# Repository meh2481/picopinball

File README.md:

# picopinball
Physical Pi Pico-Powered Pinball table heavily inspired by Space Cadet

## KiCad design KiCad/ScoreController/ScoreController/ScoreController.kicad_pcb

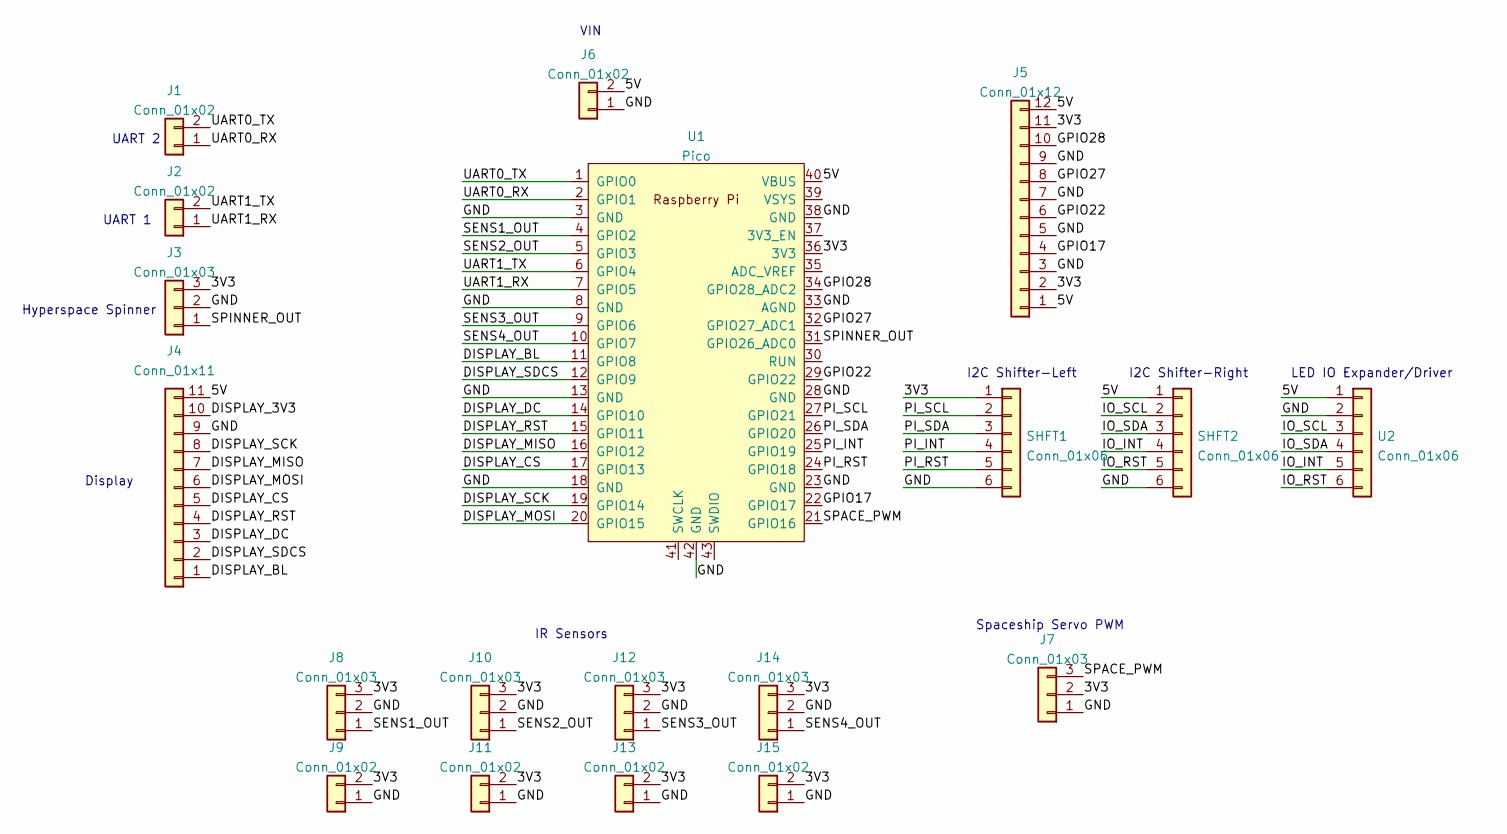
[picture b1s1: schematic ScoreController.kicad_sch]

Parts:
J1, J2, J9, J11, J13, J15: Conn_01x02; JST_XH_B2B-XH-A_1x02_P2.50mm_Vertical
J3, J8, J10, J12, J14: Conn_01x03; JST_XH_B3B-XH-A_1x03_P2.50mm_Vertical
J4: Conn_01x11; PinHeader_1x11_P2.54mm_Vertical
J5: Conn_01x12; TerminalBlock_Phoenix_MPT-0,5-12-2.54_1x12_P2.54mm_Horizont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
J6: Conn_01x02; TerminalBlock_4Ucon_1x02_P3.50mm_Horizontal
J7: Conn_01x03; PinHeader_1x03_P2.54mm_Vertical
SHFT1, SHFT2: Conn_01x06; PinHeader_1x06_P2.54mm_Vertical
U1: Pico; RPi_Pico_SMD
U2: Conn_01x06; PinHeader_1x06_P2.54mm_Vertical

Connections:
/3V3: J3.3, J5.2, J5.11, J7.2, J8.3, J9.2, J10.3, J11.2, J12.3, J13.2, J14.3, J15.2, SHFT1.1, U1.36 (3V3)
/5V: J4.11, J5.1, J5.12, J6.2, SHFT2.1, U1.40 (VBUS), U2.1
/DISPLAY_3V3: J4.10
/DISPLAY_BL: J4.1, U1.11 (GPIO8)
/DISPLAY_CS: J4.5, U1.17 (GPIO13)
/DISPLAY_DC: J4.3, U1.14 (GPIO10)
/DISPLAY_MISO: J4.7, U1.16 (GPIO12)
/DISPLAY_MOSI: J4.6, U1.20 (GPIO15)
/DISPLAY_RST: J4.4, U1.15 (GPIO11)
/DISPLAY_SCK: J4.8, U1.19 (GPIO14)
/DISPLAY_SDCS: J4.2, U1.12 (GPIO9)
/GND: J3.2, J4.9, J5.3, J5.5, J5.7, J5.9, J6.1, J7.1, J8.2, J9.1, J10.2, J11.1, J12.2, J13.1, J14.2, J15.1, SHFT1.6, SHFT2.6, U1.3 (GND), U1.8 (GND), U1.13 (GND), U1.18 (GND), U1.23 (GND), U1.28 (GND), U1.33 (AGND), U1.38 (GND), U1.42 (GND), U2.2
/GPIO17: J5.4, U1.22 (GPIO17)
/GPIO22: J5.6, U1.29 (GPIO22)
/GPIO27: J5.8, U1.32 (GPIO27_ADC1)
/GPIO28: J5.10, U1.34 (GPIO28_ADC2)
/IO_INT: SHFT2.4, U2.5
/IO_RST: SHFT2.5, U2.6
/IO_SCL: SHFT2.2, U2.3
/IO_SDA: SHFT2.3, U2.4
/PI_INT: SHFT1.4, U1.25 (GPIO19)
/PI_RST: SHFT1.5, U1.24 (GPIO18)
/PI_SCL: SHFT1.2, U1.27 (GPIO21)
/PI_SDA: SHFT1.3, U1.26 (GPIO20)
/SENS1_OUT: J8.1, U1.4 (GPIO2)
/SENS2_OUT: J10.1, U1.5 (GPIO3)
/SENS3_OUT: J12.1, U1.9 (GPIO6)
/SENS4_OUT: J14.1, U1.10 (GPIO7)
/SPACE_PWM: J7.3, U1.21 (GPIO16)
/SPINNER_OUT: J3.1, U1.31 (GPIO26_ADC0)
/UART0_RX: J1.1, U1.2 (GPIO1)
/UART0_TX: J1.2, U1.1 (GPIO0)
/UART1_RX: J2.1, U1.7 (GPIO5)
/UART1_TX: J2.2, U1.6 (GPIO4)

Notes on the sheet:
IR Sensors
Display
I2C Shifter-Right
I2C Shifter-Left
Hyperspace Spinner
Spaceship Servo PWM
UART 2
LED IO Expander/Driver
UART 1
VIN

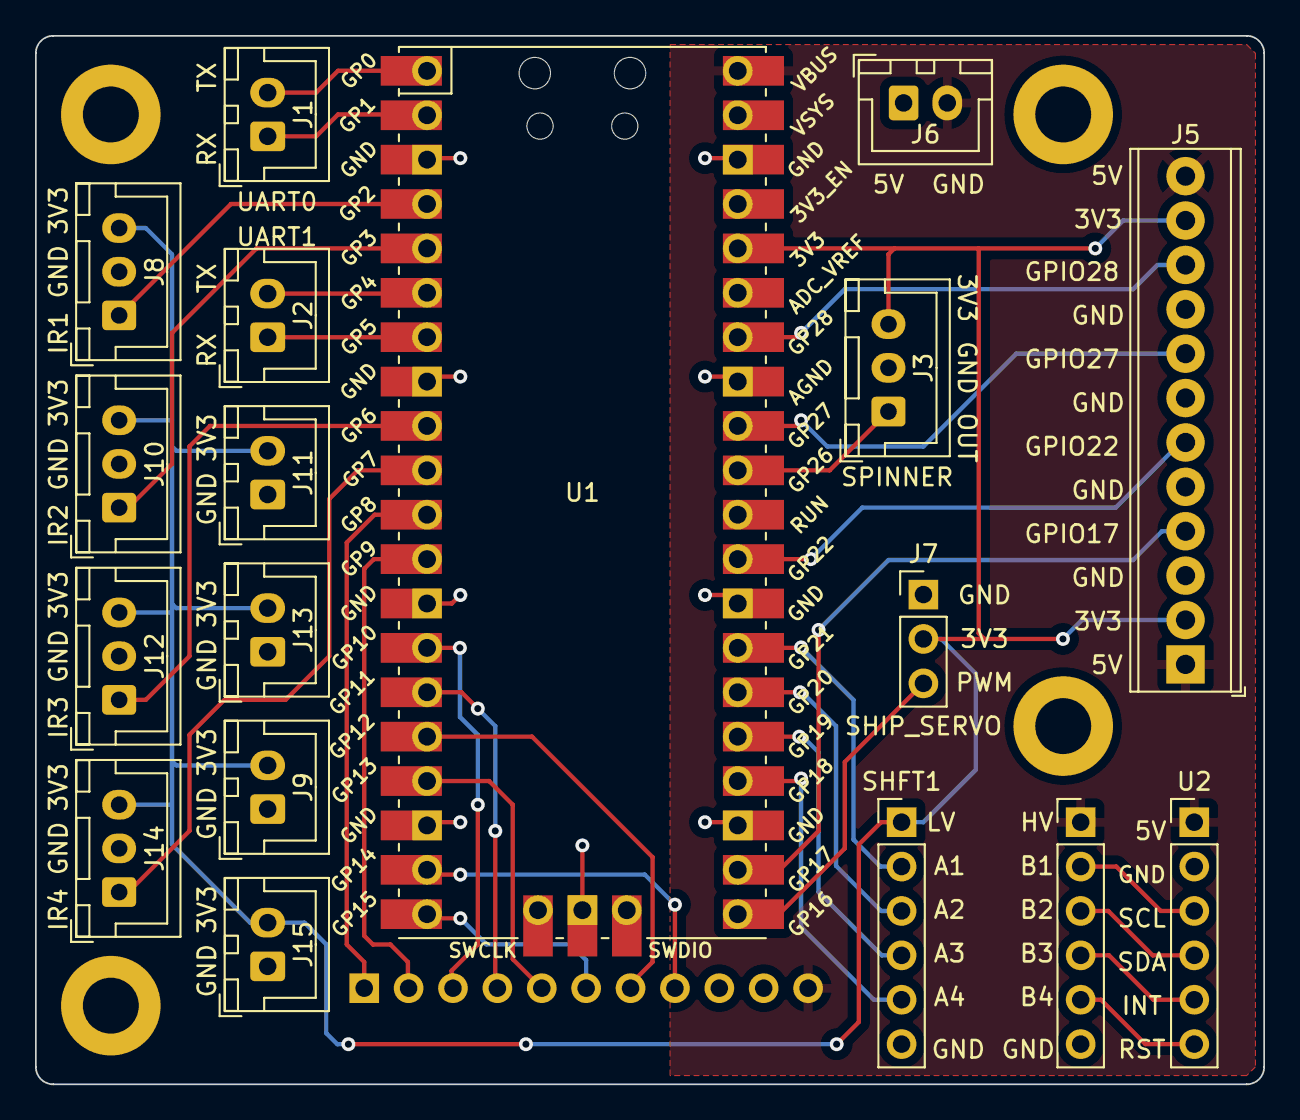
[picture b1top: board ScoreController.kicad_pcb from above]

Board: 2 copper layers, 70.3 x 60.0 mm, 23 parts (1 on the bottom side), 33 nets.

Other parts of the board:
HOLE1, HOLE1#2, HOLE2, HOLE2#2: MountingHole_3.2mm_M3_ISO7380_Pad

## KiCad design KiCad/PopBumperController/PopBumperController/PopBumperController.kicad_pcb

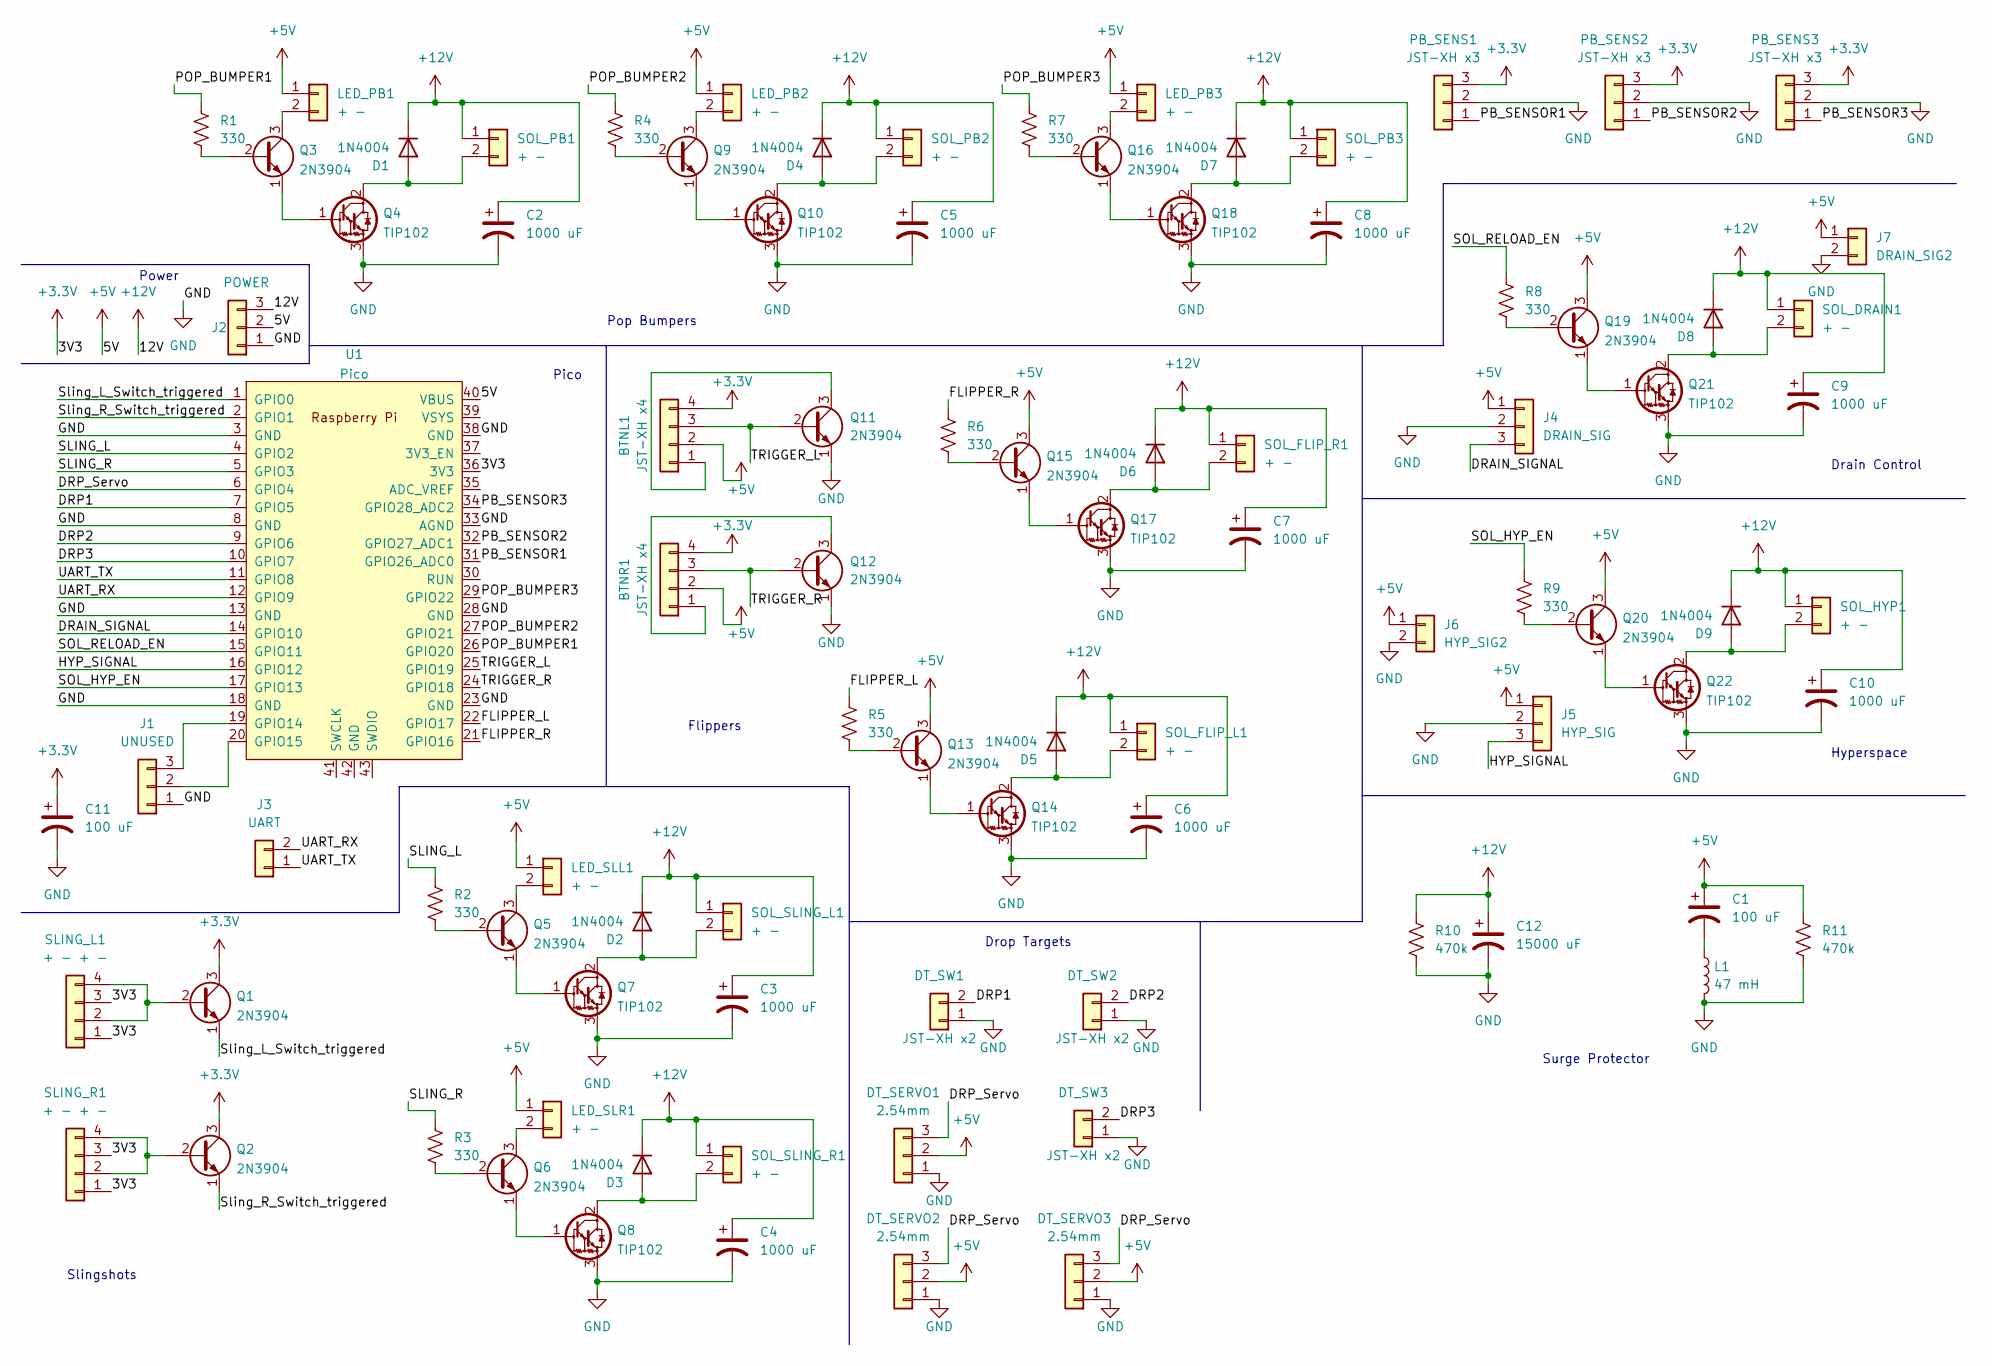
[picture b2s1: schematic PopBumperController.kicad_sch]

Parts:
BTNL1: JST-XH x4; JST_XH_B4B-XH-A_1x04_P2.50mm_Vertical
BTNR1: JST-XH x4; JST_XH_B4B-XH-A_1x04_P2.50mm_Vertical
C1, C11: 100 uF; CP_Radial_D8.0mm_P3.50mm
C2, C3, C4, C5, C6, C7, C8, C9, C10: 1000 uF; CP_Radial_D10.0mm_P5.00mm
C12: 15000 uF; CP_Radial_D25.0mm_P10.00mm_SnapIn
D1, D2, D3, D4, D5, D6, D7, D8, D9: 1N4004; D_DO-41_SOD81_P10.16mm_Horizontal
DT_SERVO1, DT_SERVO2, DT_SERVO3: 2.54mm; PinHeader_1x03_P2.54mm_Vertical
DT_SW1, DT_SW2, DT_SW3: JST-XH x2; JST_XH_B2B-XH-A_1x02_P2.50mm_Vertical
J1: UNUSED; JST_XH_B3B-XH-A_1x03_P2.50mm_Vertical
J2: POWER; JST_XH_B3B-XH-A_1x03_P2.50mm_Vertical
J3: UART; JST_XH_B2B-XH-A_1x02_P2.50mm_Vertical
J4: DRAIN_SIG; JST_XH_B3B-XH-A_1x03_P2.50mm_Vertical
J5: HYP_SIG; JST_XH_B3B-XH-A_1x03_P2.50mm_Vertical
J6: HYP_SIG2; JST_XH_B2B-XH-A_1x02_P2.50mm_Vertical
J7: DRAIN_SIG2; JST_XH_B2B-XH-A_1x02_P2.50mm_Vertical
L1: 47 mH; L_Radial_D12.0mm_P5.00mm_Fastron_11P
LED_PB1, LED_PB2, LED_PB3: + -; JST_XH_B2B-XH-A_1x02_P2.50mm_Vertical
LED_SLL1: + -; JST_XH_B2B-XH-A_1x02_P2.50mm_Vertical
LED_SLR1: + -; JST_XH_B2B-XH-A_1x02_P2.50mm_Vertical
PB_SENS1, PB_SENS2, PB_SENS3: JST-XH x3; JST_XH_B3B-XH-A_1x03_P2.50mm_Vertical
Q1, Q2, Q3, Q5, Q6, Q9, Q11, Q12, Q13, Q15, Q16, Q19, Q20: 2N3904; TO-92_Inline
Q4, Q7, Q8, Q10, Q14, Q17, Q18, Q21, Q22: TIP102; TO-220-3_Vertical
R1, R2, R3, R4, R5, R6, R7, R8, R9: 330; R_Axial_DIN0309_L9.0mm_D3.2mm_P12.70mm_Horizontal
R10, R11: 470k; R_Axial_DIN0309_L9.0mm_D3.2mm_P12.70mm_Horizontal
SLING_L1: + - + -; JST_XH_B4B-XH-A_1x04_P2.50mm_Vertical
SLING_R1: + - + -; JST_XH_B4B-XH-A_1x04_P2.50mm_Vertical
SOL_DRAIN1: + -; JST_XH_B2B-XH-A_1x02_P2.50mm_Vertical
SOL_FLIP_L1: + -; JST_XH_B2B-XH-A_1x02_P2.50mm_Vertical
SOL_FLIP_R1: + -; JST_XH_B2B-XH-A_1x02_P2.50mm_Vertical
SOL_HYP1: + -; JST_XH_B2B-XH-A_1x02_P2.50mm_Vertical
SOL_PB1, SOL_PB2, SOL_PB3: + -; JST_XH_B2B-XH-A_1x02_P2.50mm_Vertical
SOL_SLING_L1: + -; JST_XH_B2B-XH-A_1x02_P2.50mm_Vertical
SOL_SLING_R1: + -; JST_XH_B2B-XH-A_1x02_P2.50mm_Vertical
U1: Pico; RPi_Pico_TH

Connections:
+3V3: BTNL1.4, BTNR1.4, C11.1, PB_SENS1.3, PB_SENS2.3, PB_SENS3.3, Q1.3 (C), Q2.3 (C), SLING_L1.1, SLING_L1.3, SLING_R1.1, SLING_R1.3, U1.36 (3V3); also elsewhere on the board
+5V: BTNL1.2, BTNR1.2, C1.1, DT_SERVO1.2, DT_SERVO2.2, DT_SERVO3.2, J2.2, J4.1, J5.1, J6.1, J7.1, LED_PB1.1, LED_PB2.1, LED_PB3.1, LED_SLL1.1, LED_SLR1.1, Q13.3 (C), Q15.3 (C), Q19.3 (C), Q20.3 (C), R11.1, U1.40 (VBUS); also elsewhere on the board
+12V: C2.1, C3.1, C4.1, C5.1, C6.1, C7.1, C8.1, C9.1, C10.1, C12.1, D1.1 (K), D2.1 (K), D3.1 (K), D4.1 (K), D5.1 (K), D6.1 (K), D7.1 (K), D8.1 (K), D9.1 (K), J2.3, R10.1, SOL_DRAIN1.1, SOL_FLIP_L1.1, SOL_FLIP_R1.1, SOL_HYP1.1, SOL_PB1.1, SOL_PB2.1, SOL_PB3.1, SOL_SLING_L1.1, SOL_SLING_R1.1; also elsewhere on the board
/DRAIN_SIGNAL: J4.3, U1.14 (GPIO10)
/DRP1: DT_SW1.2, U1.7 (GPIO5)
/DRP2: DT_SW2.2, U1.9 (GPIO6)
/DRP3: DT_SW3.2, U1.10 (GPIO7)
/DRP_Servo: DT_SERVO1.3, DT_SERVO2.3, DT_SERVO3.3, U1.6 (GPIO4)
/FLIPPER_L: R5.1, U1.22 (GPIO17)
/FLIPPER_R: R6.1, U1.21 (GPIO16)
/HYP_SIGNAL: J5.3, U1.16 (GPIO12)
/PB_SENSOR1: PB_SENS1.1, U1.31 (GPIO26_ADC0)
/PB_SENSOR2: PB_SENS2.1, U1.32 (GPIO27_ADC1)
/PB_SENSOR3: PB_SENS3.1, U1.34 (GPIO28_ADC2)
/POP_BUMPER1: R1.1, U1.26 (GPIO20)
/POP_BUMPER2: R4.1, U1.27 (GPIO21)
/POP_BUMPER3: R7.1, U1.29 (GPIO22)
/SLING_L: R2.1, U1.4 (GPIO2)
/SLING_R: R3.1, U1.5 (GPIO3)
/SOL_HYP_EN: R9.1, U1.17 (GPIO13)
/SOL_RELOAD_EN: R8.1, U1.15 (GPIO11)
/Sling_L_Switch_triggered: Q1.1 (E), U1.1 (GPIO0)
/Sling_R_Switch_triggered: Q2.1 (E), U1.2 (GPIO1)
/TRIGGER_L: BTNL1.3, Q11.2 (B), U1.25 (GPIO19); also elsewhere on the board
/TRIGGER_R: BTNR1.3, Q12.2 (B), U1.24 (GPIO18); also elsewhere on the board
/UART_RX: J3.2, U1.12 (GPIO9)
/UART_TX: J3.1, U1.11 (GPIO8)
GND: C2.2, C3.2, C4.2, C5.2, C6.2, C7.2, C8.2, C9.2, C10.2, C11.2, C12.2, DT_SERVO1.1, DT_SERVO2.1, DT_SERVO3.1, DT_SW1.1, DT_SW2.1, DT_SW3.1, J1.1, J2.1, J4.2, J5.2, J6.2, J7.2, L1.2, PB_SENS1.2, PB_SENS2.2, PB_SENS3.2, Q4.3 (E), Q7.3 (E), Q8.3 (E), Q10.3 (E), Q11.1 (E), Q12.1 (E), Q14.3 (E), Q17.3 (E), Q18.3 (E), Q21.3 (E), Q22.3 (E), R10.2, R11.2, U1.3 (GND), U1.8 (GND), U1.13 (GND), U1.18 (GND), U1.23 (GND), U1.28 (GND), U1.33 (AGND), U1.38 (GND)
unnamed 28: BTNL1.1, Q11.3 (C); also elsewhere on the board
unnamed 29: BTNR1.1, Q12.3 (C); also elsewhere on the board
unnamed: C1.2, L1.1
unnamed: D2.2 (A), Q7.2 (C), SOL_SLING_L1.2
unnamed: D3.2 (A), Q8.2 (C), SOL_SLING_R1.2
unnamed: D4.2 (A), Q10.2 (C), SOL_PB2.2
unnamed 34: D5.2 (A), Q14.2 (C), SOL_FLIP_L1.2; also elsewhere on the board
unnamed: D6.2 (A), Q17.2 (C), SOL_FLIP_R1.2
unnamed: D7.2 (A), Q18.2 (C), SOL_PB3.2
unnamed: D8.2 (A), Q21.2 (C), SOL_DRAIN1.2
unnamed: D9.2 (A), Q22.2 (C), SOL_HYP1.2
unnamed: LED_PB1.2, Q3.3 (C)
unnamed: LED_PB2.2, Q9.3 (C)
unnamed: LED_PB3.2, Q16.3 (C)
unnamed: LED_SLL1.2, Q5.3 (C)
unnamed: LED_SLR1.2, Q6.3 (C)
unnamed: Q3.1 (E), Q4.1 (B)
unnamed: Q3.2 (B), R1.2
unnamed: Q5.1 (E), Q7.1 (B)
unnamed: Q5.2 (B), R2.2
unnamed: Q6.1 (E), Q8.1 (B)
unnamed: Q6.2 (B), R3.2
unnamed: Q9.2 (B), R4.2
unnamed: Q9.1 (E), Q10.1 (B)
unnamed: Q13.1 (E), Q14.1 (B)
unnamed: Q13.2 (B), R5.2
unnamed: Q15.1 (E), Q17.1 (B)
unnamed: Q15.2 (B), R6.2
unnamed: Q16.1 (E), Q18.1 (B)
unnamed: Q16.2 (B), R7.2
unnamed: Q19.1 (E), Q21.1 (B)
unnamed: Q19.2 (B), R8.2
unnamed: Q20.1 (E), Q22.1 (B)
unnamed: Q20.2 (B), R9.2
unnamed: Q1.2 (B), SLING_L1.2, SLING_L1.4
unnamed: Q2.2 (B), SLING_R1.2, SLING_R1.4
unnamed: D1.2 (A), Q4.2 (C), SOL_PB1.2
unnamed: J1.3, U1.19 (GPIO14)
unnamed: J1.2, U1.20 (GPIO15)

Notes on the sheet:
Pico
Surge Protector
Hyperspace
Flippers
Power
Drain Control
Slingshots
Drop Targets
Pop Bumpers

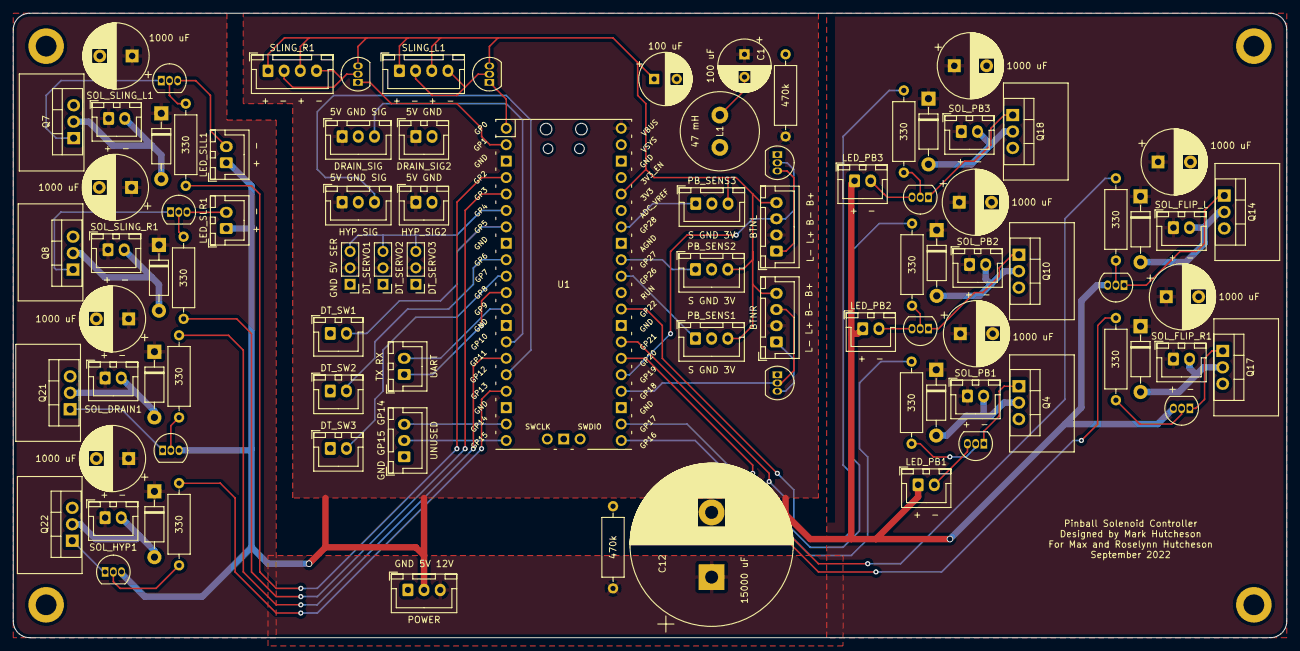
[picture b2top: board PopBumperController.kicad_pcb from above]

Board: 2 copper layers, 196.8 x 96.5 mm, 90 parts (0 on the bottom side), 67 nets.

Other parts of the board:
BTNL: JST-XH x4; JST_XH_B4B-XH-A_1x04_P2.50mm_Vertical
BTNR: JST-XH x4; JST_XH_B4B-XH-A_1x04_P2.50mm_Vertical
SOL_FLIP_L: + -; JST_XH_B2B-XH-A_1x02_P2.50mm_Vertical

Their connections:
+3V3: BTNL.4, BTNR.4; also elsewhere on the board
+5V: BTNL.2, BTNR.2; also elsewhere on the board
+12V: SOL_FLIP_L.1; also elsewhere on the board
/TRIGGER_L: BTNL.3; also elsewhere on the board
/TRIGGER_R: BTNR.3; also elsewhere on the board
unnamed 28: BTNL.1; also elsewhere on the board
unnamed 29: BTNR.1; also elsewhere on the board
unnamed 34: SOL_FLIP_L.2; also elsewhere on the board

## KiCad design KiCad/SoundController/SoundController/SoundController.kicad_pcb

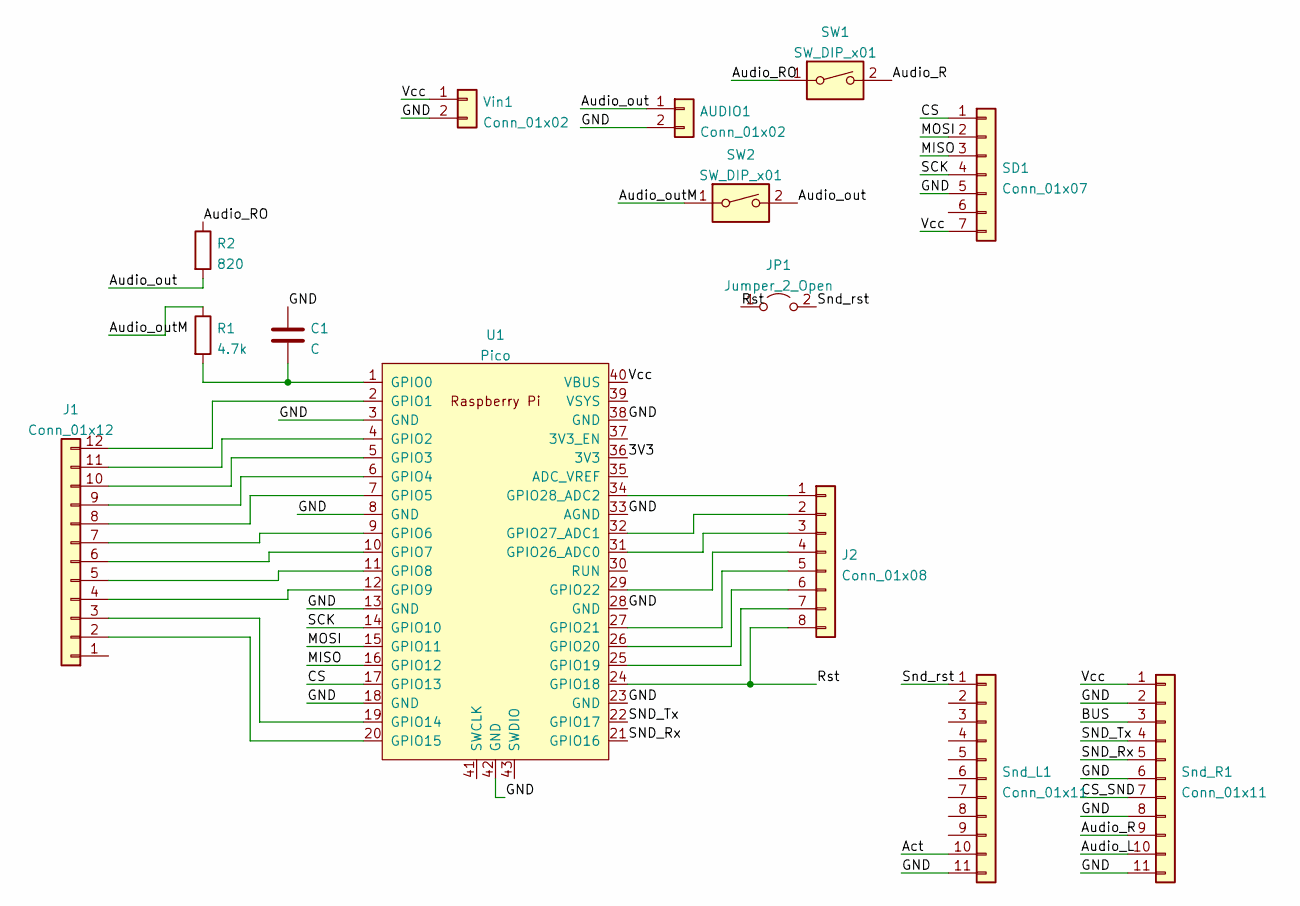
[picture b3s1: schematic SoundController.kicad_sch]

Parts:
AUDIO1: Conn_01x02; TerminalBlock_4Ucon_1x02_P3.50mm_Horizontal
C1: C; C_Disc_D7.5mm_W4.4mm_P5.00mm
J1: Conn_01x12; PinHeader_1x12_P2.54mm_Vertical
J2: Conn_01x08; PinHeader_1x08_P2.54mm_Vertical
JP1: Jumper_2_Open; PinHeader_1x02_P2.54mm_Vertical
R1: 4.7k; R_Axial_DIN0309_L9.0mm_D3.2mm_P15.24mm_Horizontal
R2: 820; R_Axial_DIN0309_L9.0mm_D3.2mm_P15.24mm_Horizontal
SD1: Conn_01x07; PinHeader_1x07_P2.54mm_Vertical
SW1, SW2: SW_DIP_x01; TerminalBlock_4Ucon_1x02_P3.50mm_Horizontal
Snd_L1: Conn_01x11; PinHeader_1x11_P2.54mm_Vertical
Snd_R1: Conn_01x11; PinHeader_1x11_P2.54mm_Vertical
U1: Pico; RPi_Pico_SMD_TH
Vin1: Conn_01x02; TerminalBlock_4Ucon_1x02_P3.50mm_Horizontal

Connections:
/3V3: U1.36 (3V3)
/Act: Snd_L1.10
/Audio_L: Snd_R1.10
/Audio_R: SW1.2, Snd_R1.9
/Audio_RO: R2.1, SW1.1
/Audio_out: AUDIO1.1, R2.2, SW2.2
/Audio_outM: R1.1, SW2.1
/BUS: Snd_R1.3
/CS: SD1.1, U1.17 (GPIO13)
/CS_SND: Snd_R1.7
/GND: AUDIO1.2, C1.1, SD1.5, Snd_L1.11, Snd_R1.2, Snd_R1.6, Snd_R1.8, Snd_R1.11, U1.3 (GND), U1.8 (GND), U1.13 (GND), U1.18 (GND), U1.23 (GND), U1.28 (GND), U1.33 (AGND), U1.38 (GND), U1.42 (GND), Vin1.2
/MISO: SD1.3, U1.16 (GPIO12)
/MOSI: SD1.2, U1.15 (GPIO11)
/Rst: J2.8, JP1.1 (A), U1.24 (GPIO18)
/SCK: SD1.4, U1.14 (GPIO10)
/SND_Rx: Snd_R1.5, U1.21 (GPIO16)
/SND_Tx: Snd_R1.4, U1.22 (GPIO17)
/Snd_rst: JP1.2 (B), Snd_L1.1
/Vcc: SD1.7, Snd_R1.1, U1.40 (VBUS), Vin1.1
unnamed: C1.2, R1.2, U1.1 (GPIO0)
unnamed: J1.2, U1.20 (GPIO15)
unnamed: J1.3, U1.19 (GPIO14)
unnamed: J1.4, U1.12 (GPIO9)
unnamed: J1.5, U1.11 (GPIO8)
unnamed: J1.6, U1.10 (GPIO7)
unnamed: J1.7, U1.9 (GPIO6)
unnamed: J1.8, U1.7 (GPIO5)
unnamed: J1.9, U1.6 (GPIO4)
unnamed: J1.10, U1.5 (GPIO3)
unnamed: J1.11, U1.4 (GPIO2)
unnamed: J1.12, U1.2 (GPIO1)
unnamed: J2.1, U1.34 (GPIO28_ADC2)
unnamed: J2.2, U1.32 (GPIO27_ADC1)
unnamed: J2.3, U1.31 (GPIO26_ADC0)
unnamed: J2.4, U1.29 (GPIO22)
unnamed: J2.5, U1.27 (GPIO21)
unnamed: J2.6, U1.26 (GPIO20)
unnamed: J2.7, U1.25 (GPIO19)

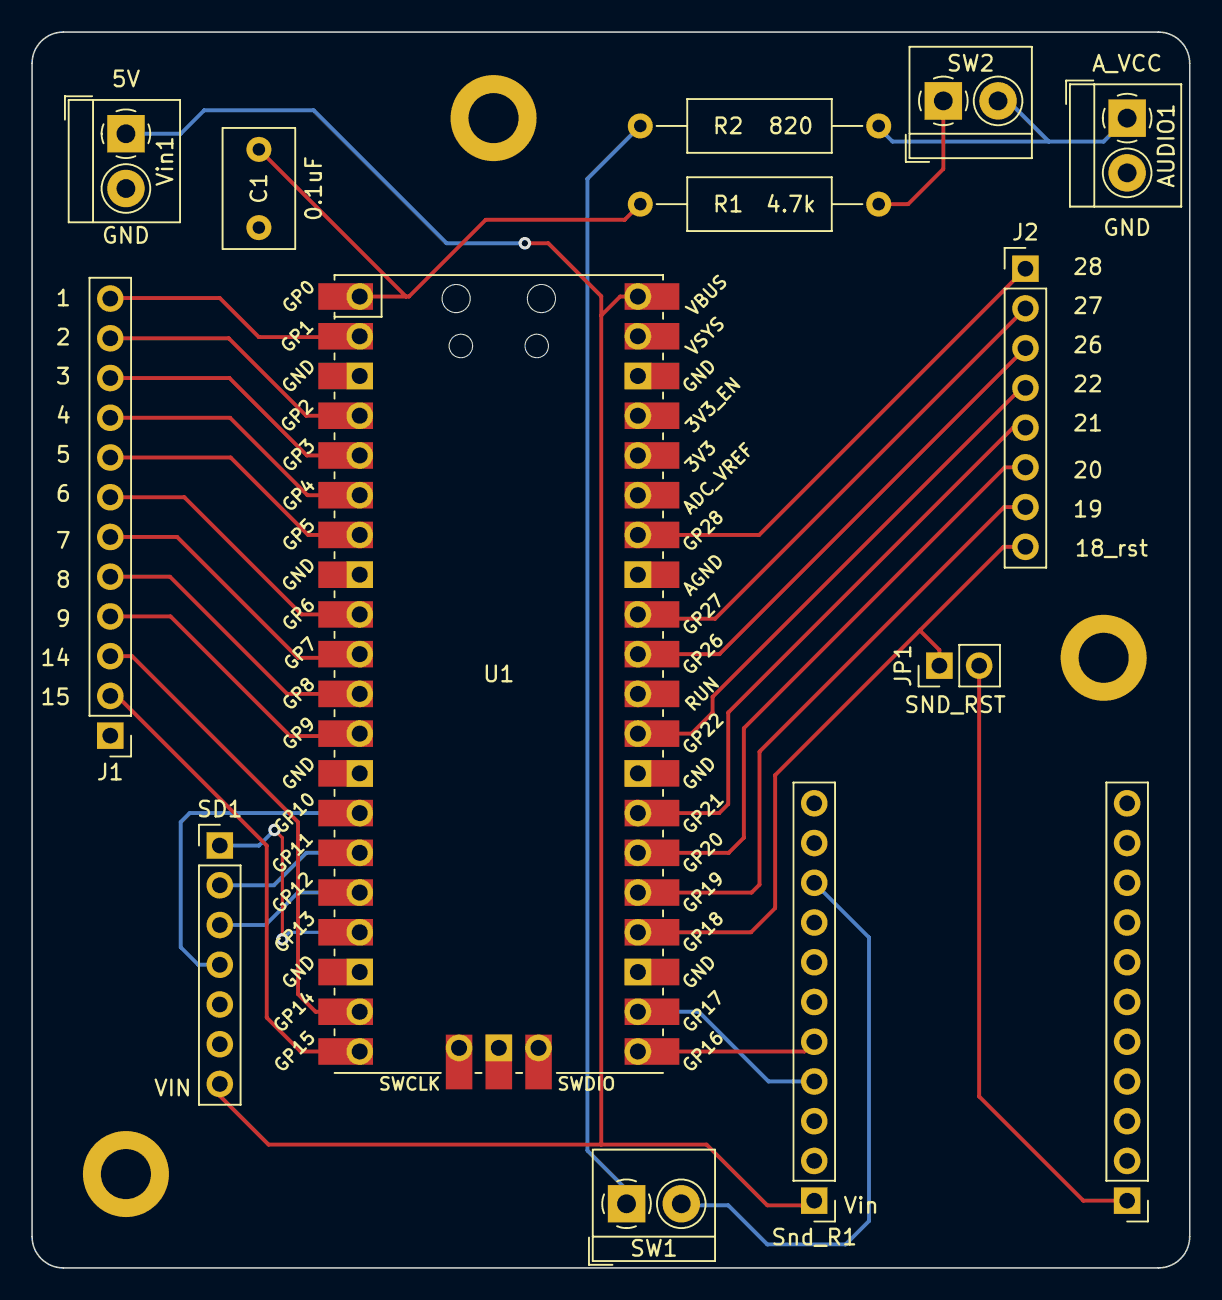
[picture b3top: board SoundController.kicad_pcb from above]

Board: 2 copper layers, 74.0 x 79.0 mm, 14 parts (0 on the bottom side), 33 nets.

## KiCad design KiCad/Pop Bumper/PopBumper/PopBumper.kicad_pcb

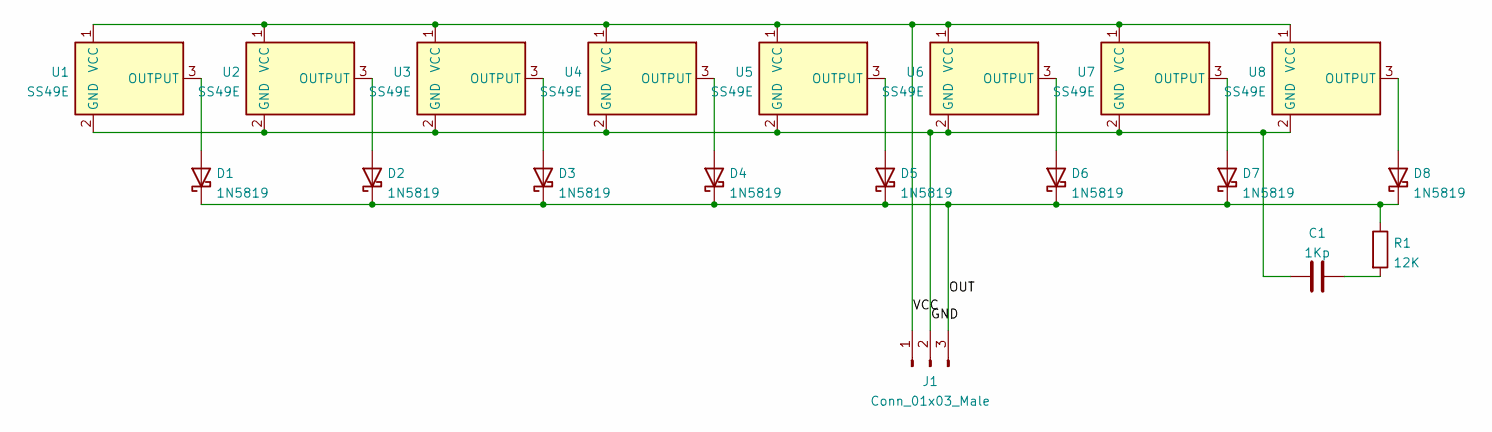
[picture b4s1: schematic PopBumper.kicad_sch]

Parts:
C1: 1Kp; C_Disc_D5.1mm_W3.2mm_P5.00mm
D1, D2, D3, D4, D5, D6, D7, D8: 1N5819; D_DO-41_SOD81_P10.16mm_Horizontal
J1: Conn_01x03_Male; PinHeader_1x03_P2.54mm_Vertical
R1: 12K; R_Axial_DIN0309_L9.0mm_D3.2mm_P2.54mm_Vertical
U1, U2, U3, U4, U5, U6, U7, U8: SS49E; PinHeader_1x03_P1.27mm_Vertical

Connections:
/GND: C1.1, J1.2, U1.2 (GND), U2.2 (GND), U3.2 (GND), U4.2 (GND), U5.2 (GND), U6.2 (GND), U7.2 (GND), U8.2 (GND)
/OUT: D1.1 (K), D2.1 (K), D3.1 (K), D4.1 (K), D5.1 (K), D6.1 (K), D7.1 (K), D8.1 (K), J1.3, R1.1
/VCC: J1.1, U1.1 (VCC), U2.1 (VCC), U3.1 (VCC), U4.1 (VCC), U5.1 (VCC), U6.1 (VCC), U7.1 (VCC), U8.1 (VCC)
unnamed: D1.2 (A), U1.3 (OUTPUT)
unnamed: D2.2 (A), U2.3 (OUTPUT)
unnamed: D4.2 (A), U4.3 (OUTPUT)
unnamed: D5.2 (A), U5.3 (OUTPUT)
unnamed: D6.2 (A), U6.3 (OUTPUT)
unnamed: D7.2 (A), U7.3 (OUTPUT)
unnamed: C1.2, R1.2
unnamed: D3.2 (A), U3.3 (OUTPUT)
unnamed: D8.2 (A), U8.3 (OUTPUT)

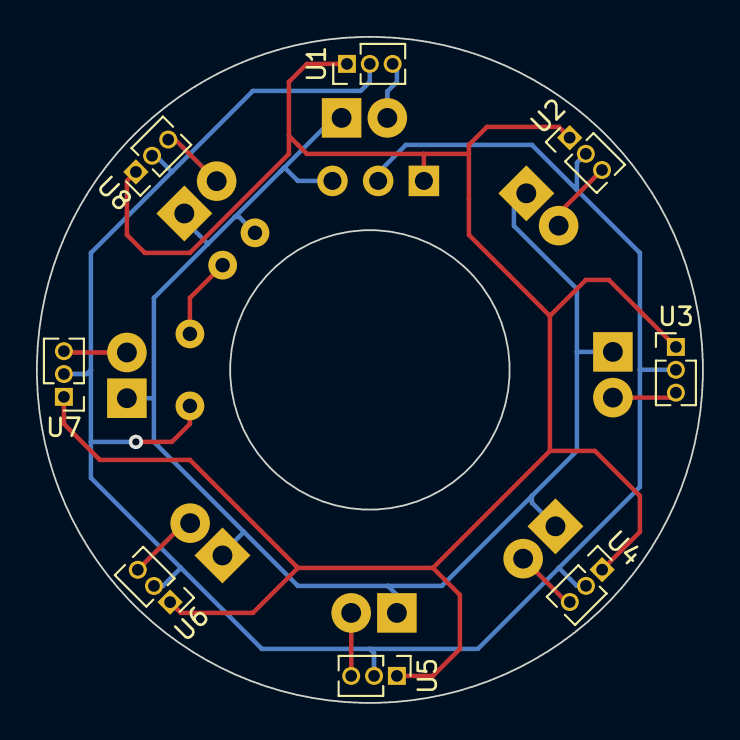
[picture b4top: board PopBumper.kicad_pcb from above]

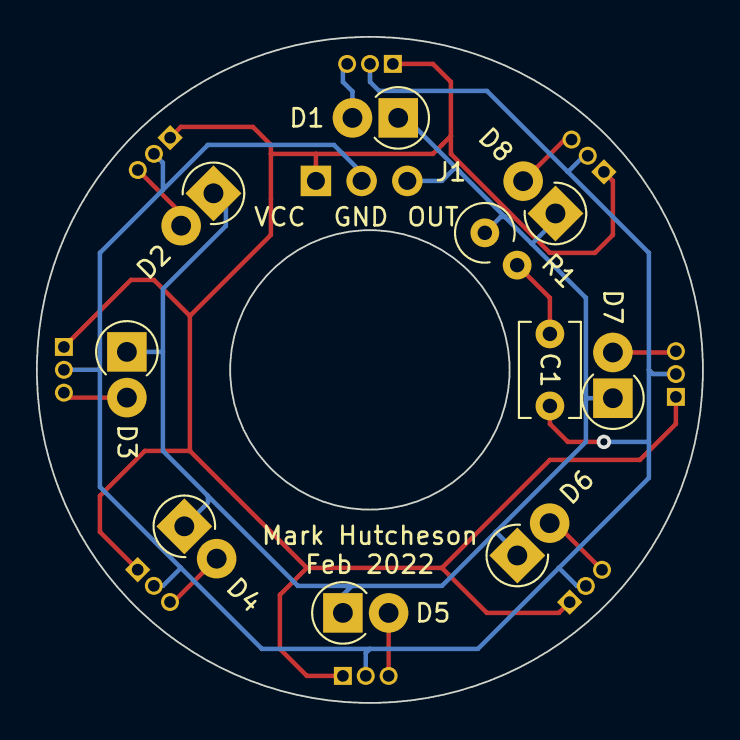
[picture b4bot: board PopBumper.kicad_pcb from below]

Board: 2 copper layers, 37.0 x 37.0 mm, 19 parts (11 on the bottom side), 12 nets.

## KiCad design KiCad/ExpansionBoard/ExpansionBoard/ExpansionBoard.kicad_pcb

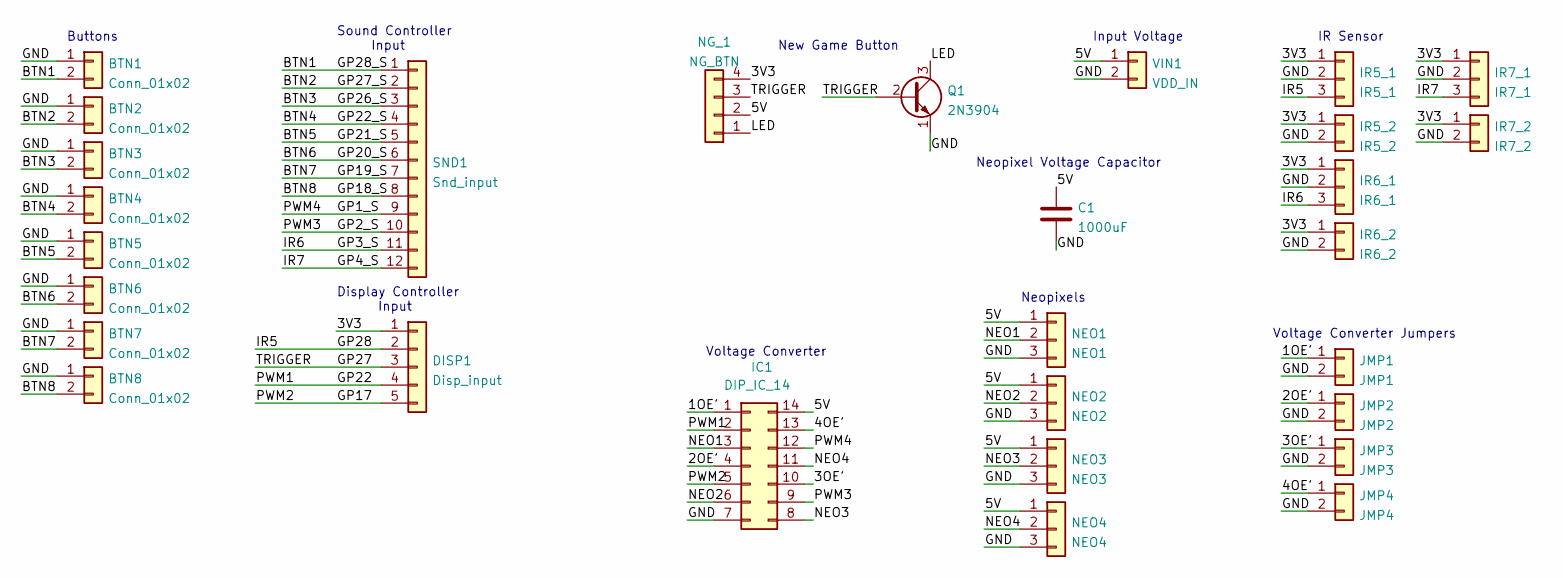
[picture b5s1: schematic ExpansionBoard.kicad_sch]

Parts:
BTN1, BTN2, BTN3, BTN4, BTN5, BTN6, BTN7, BTN8: Conn_01x02; JST_XH_B2B-XH-A_1x02_P2.50mm_Vertical
C1: 1000uF; CP_Radial_D10.0mm_P5.00mm
DISP1: Disp_input; JST_XH_B5B-XH-A_1x05_P2.50mm_Vertical
IC1: DIP_IC_14; DIP-14_W7.62mm_LongPads
IR5_1: IR5_1; JST_XH_B3B-XH-A_1x03_P2.50mm_Vertical
IR5_2: IR5_2; JST_XH_B2B-XH-A_1x02_P2.50mm_Vertical
IR6_1: IR6_1; JST_XH_B3B-XH-A_1x03_P2.50mm_Vertical
IR6_2: IR6_2; JST_XH_B2B-XH-A_1x02_P2.50mm_Vertical
IR7_1: IR7_1; JST_XH_B3B-XH-A_1x03_P2.50mm_Vertical
IR7_2: IR7_2; JST_XH_B2B-XH-A_1x02_P2.50mm_Vertical
JMP1: JMP1; PinHeader_1x02_P2.54mm_Vertical
JMP2: JMP2; PinHeader_1x02_P2.54mm_Vertical
JMP3: JMP3; PinHeader_1x02_P2.54mm_Vertical
JMP4: JMP4; PinHeader_1x02_P2.54mm_Vertical
NEO1: NEO1; JST_PH_B3B-PH-K_1x03_P2.00mm_Vertical
NEO2: NEO2; JST_PH_B3B-PH-K_1x03_P2.00mm_Vertical
NEO3: NEO3; JST_PH_B3B-PH-K_1x03_P2.00mm_Vertical
NEO4: NEO4; JST_PH_B3B-PH-K_1x03_P2.00mm_Vertical
NG_1: NG_BTN; JST_XH_B4B-XH-A_1x04_P2.50mm_Vertical
Q1: 2N3904; TO-92_Inline
SND1: Snd_input; TerminalBlock_Phoenix_MPT-0,5-12-2.54_1x12_P2.54mm_Horizont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
VIN1: VDD_IN; JST_XH_B2B-XH-A_1x02_P2.50mm_Vertical

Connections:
/1OE': IC1.1, JMP1.1
/2OE': IC1.4, JMP2.1
/3OE': IC1.10, JMP3.1
/3V3: DISP1.1, IR5_1.1, IR5_2.1, IR6_1.1, IR6_2.1, IR7_1.1, IR7_2.1, NG_1.4
/4OE': IC1.13, JMP4.1
/5V: C1.1, IC1.14, NEO1.1, NEO2.1, NEO3.1, NEO4.1, NG_1.2, VIN1.1
/BTN1: BTN1.2, SND1.1
/BTN2: BTN2.2, SND1.2
/BTN3: BTN3.2, SND1.3
/BTN4: BTN4.2, SND1.4
/BTN5: BTN5.2, SND1.5
/BTN6: BTN6.2, SND1.6
/BTN7: BTN7.2, SND1.7
/BTN8: BTN8.2, SND1.8
/GND: BTN1.1, BTN2.1, BTN3.1, BTN4.1, BTN5.1, BTN6.1, BTN7.1, BTN8.1, C1.2, IC1.7, IR5_1.2, IR5_2.2, IR6_1.2, IR6_2.2, IR7_1.2, IR7_2.2, JMP1.2, JMP2.2, JMP3.2, JMP4.2, NEO1.3, NEO2.3, NEO3.3, NEO4.3, Q1.1 (E), VIN1.2
/GP3_S: IR6_1.3, SND1.11
/GP4_S: IR7_1.3, SND1.12
/IR5: DISP1.2, IR5_1.3
/LED: NG_1.1, Q1.3 (C)
/NEO1: IC1.3, NEO1.2
/NEO2: IC1.6, NEO2.2
/NEO3: IC1.8, NEO3.2
/NEO4: IC1.11, NEO4.2
/PWM1: DISP1.4, IC1.2
/PWM2: DISP1.5, IC1.5
/PWM3: IC1.9, SND1.10
/PWM4: IC1.12, SND1.9
/TRIGGER: DISP1.3, NG_1.3, Q1.2 (B)

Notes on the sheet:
Voltage Converter
Buttons
IR Sensor
Display Controller Input
Input Voltage
Neopixel Voltage Capacitor
Neopixels
Sound Controller Input
New Game Button
Voltage Converter Jumpers

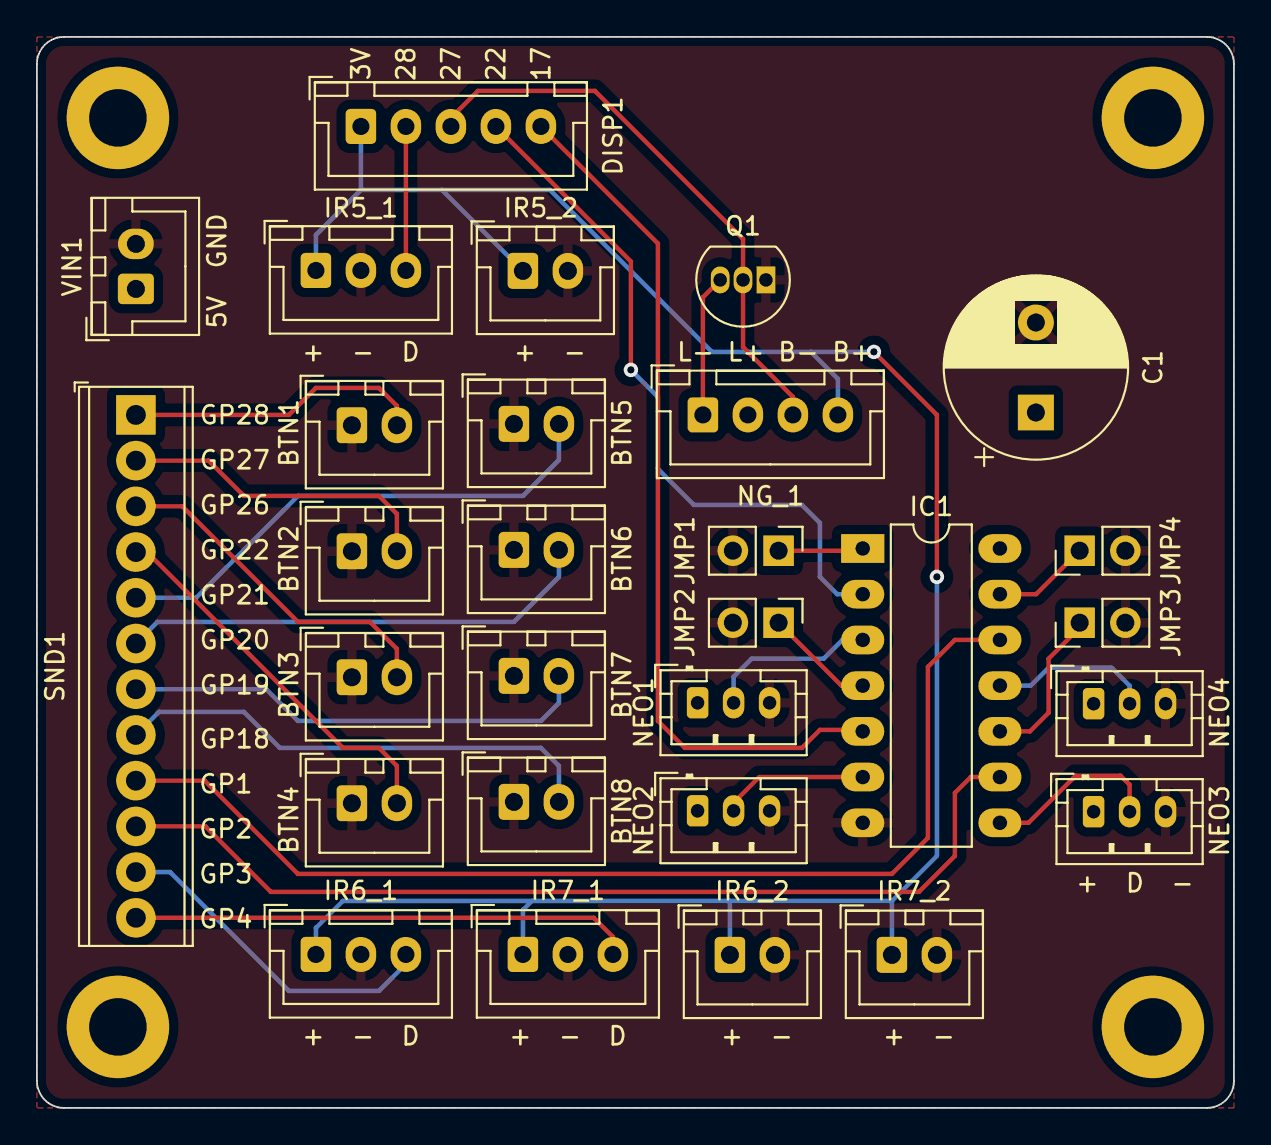
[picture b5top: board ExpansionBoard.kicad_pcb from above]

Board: 2 copper layers, 66.5 x 59.5 mm, 29 parts (0 on the bottom side), 28 nets.

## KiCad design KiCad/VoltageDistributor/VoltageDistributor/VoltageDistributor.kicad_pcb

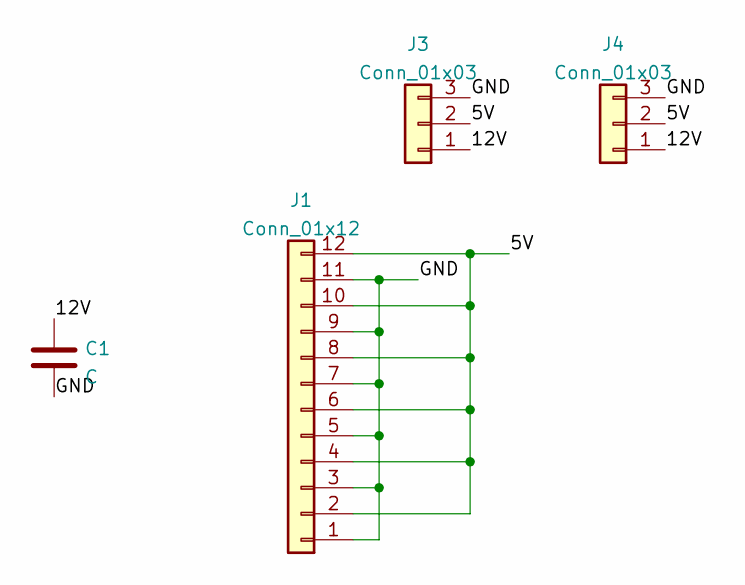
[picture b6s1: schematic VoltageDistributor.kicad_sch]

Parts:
C1: C; CP_Radial_D25.0mm_P10.00mm_SnapIn
J1: Conn_01x12; TerminalBlock_Phoenix_MPT-0,5-12-2.54_1x12_P2.54mm_Horizont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
J3, J4: Conn_01x03; JST_XH_B3B-XH-A_1x03_P2.50mm_Vertical

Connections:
/5V: J1.2, J1.4, J1.6, J1.8, J1.10, J1.12, J3.2, J4.2
/12V: C1.1, J3.1, J4.1
/GND: C1.2, J1.1, J1.3, J1.5, J1.7, J1.9, J1.11, J3.3, J4.3

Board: 2 copper layers, 4 parts (0 on the bottom side), 3 nets, no tracks yet.
